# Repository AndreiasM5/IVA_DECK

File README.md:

<div align="center">

# IVA DECK

### A custom ESP32 macro keyboard with a desktop companion and behavioral recognition

**9 mechanical keys · 3 volume controls · LCD + microSD · USB / Bluetooth · Python + PyQt6**

[Download Windows app](https://github.com/AndreiasM5/IVA_DECK/releases/latest) · [Install V5](docs/windows-app-v5.ro.md) · [Demo](docs/media/iva-deck-demo.mp4) · [Get started](docs/getting-started.md) · [Hardware](docs/hardware.md) · [Protocol](docs/protocol.md) · [AI experiment](docs/behavioral-recognition.md) · [Română](docs/README.ro.md)

**Designed and built by Ioan-Andrei Ivașcu**

</div>

IVA DECK combines a custom PCB, ESP32 electronics, embedded software, a Windows desktop application, and a behavioral recognition experiment. Nine programmable keys handle shortcuts and media actions, three physical knobs control application volume, and the companion app exposes the display, storage, buzzer, and proximity sensor.

The original academic project was presented in June 2025 at the Faculty of Mathematics and Computer Science, University of Bucharest, as **“Tastatură Inteligentă cu Recunoaștere Comportamentală asistată de AI.”**

## Windows app — V5

**[Download the Windows installer](https://github.com/AndreiasM5/IVA_DECK/releases/latest)** · [Ghid de instalare în română](docs/windows-app-v5.ro.md) · [Source and build instructions](SOFTWARE/APP/v5/)

Install **IVA-DECK-5.0.0-Setup-x64.exe**, pair your deck over Bluetooth or connect USB, then select its port in **Conexiune**. No separate Python installation is needed. Supports Windows 10 21H2+ / Windows 11 x64.

V5 adds a purple/pink interface, macro labels and assignment dialogs, an editable macro library and three animated potentiometers. The **Volum** page selects audio targets. Macros, audio targets and the last port are saved per user. AI and SD-image workflows are outside this release. V4 and the historical project documentation remain available.

The V5 application is free software under [GPLv3](SOFTWARE/APP/v5/LICENSE). This first installer is unsigned; see the release notes and SHA-256 checksums.

## See it working

**[Full demonstration with audio — 2 min 8 sec](docs/media/iva-deck-demo.mp4)**

The recording shows key presses, macro configuration, audio controls, proximity feedback, display interaction, and behavioral analysis. The GIF is a silent excerpt. Open or download the MP4 for the complete recording.

## What I built

| Layer | Contribution |
| --- | --- |
| Hardware | Custom KiCad PCBs, 3×3 key matrix, three potentiometers, peripheral integration, and enclosure |
| Embedded | ESP32 peripheral control and bidirectional serial messaging |
| Desktop | PyQt6 interface for macros, Windows volume control, device commands, and logging |
| AI experiment | Feature extraction and Random Forest recognition using keys, timing, distance, and volume |

## Desktop companion

| Live keys | Application volume |
| --- | --- |
|  |  |

| Macros | Display and storage |
| --- | --- |
|  |  |

The application targets **Windows**, using `pycaw` and Windows COM APIs for audio-session control. Its interface is in Romanian.

<details>
<summary>More application screens: proximity and connections</summary>

| Proximity | Connection settings |
| --- | --- |
|  |  |

</details>

## Architecture

```mermaid
flowchart LR
  Keys[3x3 matrix] -->|GPIO| ESP[ESP32]
  Knobs[Three knobs] -->|ADC| ESP
  ToF[VL53L0X] -->|I2C| ESP
  ESP -->|SPI| LCD[ST7789]
  ESP <-->|SPI| SD[microSD]
  ESP --> Buzzer[Buzzer]
  ESP <-->|JSON over USB or Bluetooth serial| App[PyQt6 app]
  App --> Macros[OS macros]
  App --> Audio[Windows audio]
  App --> Logs[Local logs]
  Logs --> Features[Feature extraction]
  Features --> RF[Random Forest]
```

The INMP441 microphone is included in the hardware design. Full host audio streaming and voice control are unfinished, rather than demonstrated features.

## From prototype to PCB

| PCB layout | Enclosure design |
| --- | --- |
|  |  |

Original hardware iterations are preserved. Start with [revision v6](HARDWARE/v6_esp32/) and the [hardware guide](docs/hardware.md).

## Explore

| Material | Contents |
| --- | --- |
| [Getting started](docs/getting-started.md) | Windows installation and connections |
| [Desktop source](SOFTWARE/APP/v4/iva_key_app/) | PyQt6 app and configuration |
| [ESP32 v6](SOFTWARE/DECK/v6_esp32/) | Sketches and firmware status |
| [KiCad hardware](HARDWARE/) | Schematics, layouts, and production exports |
| [Protocol](docs/protocol.md) | Host messages and commands |
| [Behavioral recognition](docs/behavioral-recognition.md) | Training workflow and evaluation limits |
| [Thesis](Documentation.pdf) | Original 52-page Romanian academic documentation |
| [Presentation PDF](docs/presentation-ro.pdf) | Romanian defense presentation |
| [Editable slides](Presentation.pptx) | Original slide deck |

## Project status

The desktop source, AI script, KiCad projects, and peripheral tests are available. A complete **historical ESP32 sketch was recovered from the author's development chat** and is included with provenance and compatibility notes. It has not been verified as the exact firmware used in the demo; see the [firmware status](SOFTWARE/DECK/v6_esp32/README.md).

The thesis reports approximately **70% behavioral recognition** in its experiment. This is a historical reported result, not a newly reproduced benchmark or an authentication guarantee. See the [AI guide](docs/behavioral-recognition.md).

Documentation and media were checked against the supplied materials and repository source. Fresh hardware operation, firmware compilation, and desktop integration have not been revalidated during this documentation update.

## Author

**Ioan-Andrei Ivașcu** · [@AndreiasM5](https://github.com/AndreiasM5)

Custom hardware, firmware development, companion software, and behavioral-recognition research for the original academic project.

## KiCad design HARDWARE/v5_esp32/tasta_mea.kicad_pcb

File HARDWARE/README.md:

# IVA DECK hardware

Start with [revision v6](v6_esp32/) and the [hardware guide](../docs/hardware.md).

Original directories preserve early Arduino Micro designs and later ESP32 iterations. Use editable KiCad sources for review; screenshots in `docs/media/` are explanatory references. Manufacturing exports have not been regenerated during this update.

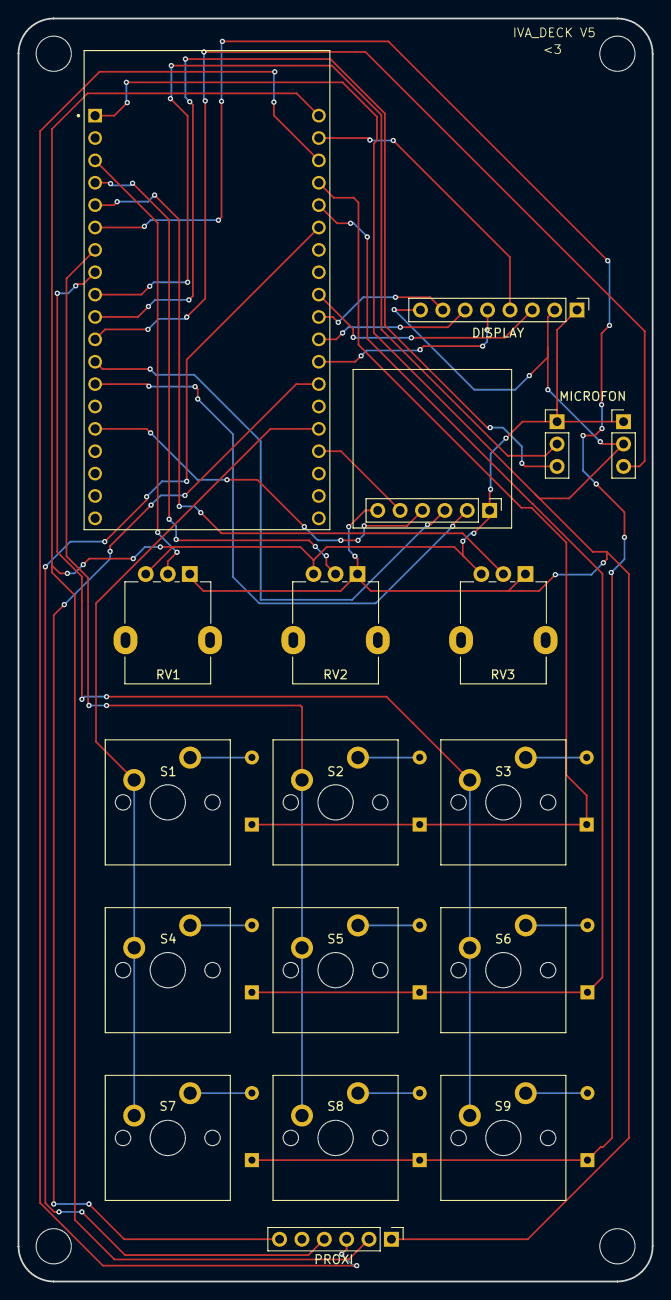
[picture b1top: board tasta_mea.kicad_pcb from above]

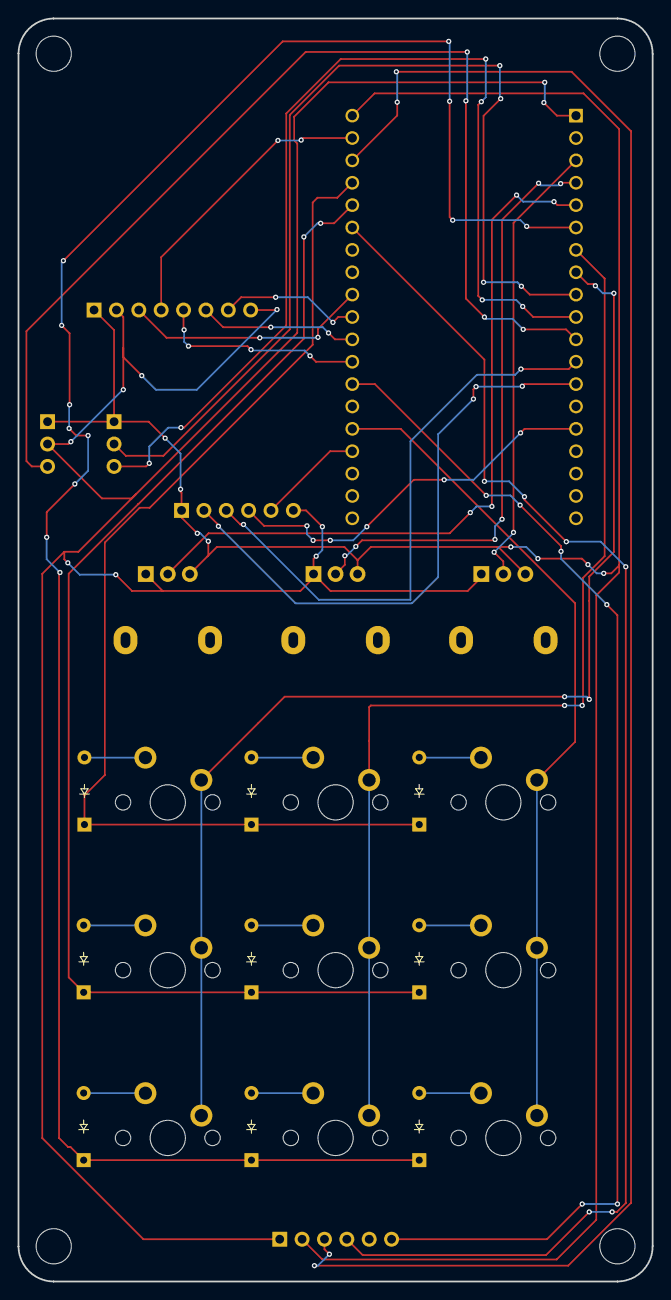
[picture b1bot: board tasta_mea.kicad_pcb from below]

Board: 2 copper layers, 72.0 x 143.4 mm, 27 parts (9 on the bottom side), 35 nets.

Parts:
D1, D2, D3, D4, D5, D6, D7, D8, D9: Diode; DO-35
DISPLAY: ST7789; PinHeader_1x08_P2.54mm_Vertical
J2: Card_reader; PinHeader_1x06_P2.54mm_Vertical
J4: IMNP441_Dreapta; PinHeader_1x03_P2.54mm_Vertical
MICROFON: IMNP441_stanga; PinHeader_1x03_P2.54mm_Vertical
PROXI: VL53L0X; PinHeader_1x06_P2.54mm_Vertical
RV1, RV2, RV3: R_Potentiometer; Potentiometer_Alpha_RD901F-40-00D_Single_Vertical
S1, S2, S3, S4, S5, S6, S7, S8, S9: Keyswitch; MX_PCB_1.00u
U3: ESP32-DEVKITC-32D; MODULE_ESP32-DEVKITC-32D

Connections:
C_clk: J2.3, U3.J2-12 (IO14)
C_cs: J2.5, U3.J3-16 (IO15)
C_gnd: DISPLAY.1, J2.1, J4.1, MICROFON.1, PROXI.2, RV1.3, RV2.3, RV3.3, U3.J3-1 (GND3)
C_miso: J2.2, U3.J2-13 (IO12)
C_mosi: J2.4, U3.J2-15 (IO13)
C_vcc: DISPLAY.2, DISPLAY.8, J2.6, J4.2, PROXI.1, RV1.1, RV2.1, RV3.1, U3.J2-1 (3V3)
D_CS: DISPLAY.7, U3.J3-10 (IO5)
D_DC: DISPLAY.6, U3.J3-11 (IO17)
D_RST: DISPLAY.5, U3.J3-12 (IO16)
D_SCL: DISPLAY.3, U3.J3-9 (IO18)
D_SDA: DISPLAY.4, U3.J3-2 (IO23)
M_SCK: MICROFON.3, U3.J2-10 (IO26)
M_SD: J4.3, U3.J2-11 (IO27)
M_WS: MICROFON.2, U3.J2-9 (IO25)
unnamed: D1.2 (A), S1.2
unnamed: D2.2 (A), S2.2
unnamed: D3.2 (A), S3.2
unnamed: D4.2 (A), S4.2
unnamed: D5.2 (A), S5.2
unnamed: D6.2 (A), S6.2
unnamed: D7.2 (A), S7.2
unnamed: D8.2 (A), S8.2
unnamed: D9.2 (A), S9.2
P_SCL: PROXI.3, U3.J3-3 (IO22)
P_SDA: PROXI.4, U3.J3-6 (IO21)
P_XSHUT: PROXI.6, U3.J3-13 (IO4)
col 1: S1.1, S4.1, S7.1, U3.J3-15 (IO2)
col 2: S2.1, S5.1, S8.1, U3.J2-7 (IO32)
col 3: S3.1, S6.1, S9.1, U3.J2-8 (IO33)
row 1: D1.1 (K), D2.1 (K), D3.1 (K), U3.J3-4 (TXD0)
row 2: D4.1 (K), D5.1 (K), D6.1 (K), U3.J3-5 (RXD0)
row 3: D7.1 (K), D8.1 (K), D9.1 (K), U3.J2-6 (IO35)
vol 1: RV1.2, U3.J2-3 (SENSOR_VP)
vol 2: RV2.2, U3.J2-4 (SENSOR_VN)
vol 3: RV3.2, U3.J2-5 (IO34)

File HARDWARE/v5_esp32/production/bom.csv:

Designator,Footprint,Quantity,Value,LCSC Part #
"D1, D2, D3, D4, D5, D6, D7, D8, D9",DO-35,9,Diode,
DISPLAY,PinHeader_1x08_P2.54mm_Vertical,1,ST7789,
J2,PinHeader_1x06_P2.54mm_Vertical,1,Card_reader,
J4,PinHeader_1x03_P2.54mm_Vertical,1,IMNP441_Dreapta,
MICROFON,PinHeader_1x03_P2.54mm_Vertical,1,IMNP441_stanga,
PROXI,PinHeader_1x06_P2.54mm_Vertical,1,VL53L0X,
"RV1, RV2, RV3",Potentiometer_Alpha_RD901F-40-00D_Single_Vertical,3,R_Potentiometer,
"S1, S2, S3, S4, S5, S6, S7, S8, S9",MX_PCB_1.00u,9,Keyswitch,
U3,MODULE_ESP32-DEVKITC-32D,1,ESP32-DEVKITC-32D,

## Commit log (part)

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2025-03-27 hardware deck v1_arduino_micro
2025-03-27 hardware deck v1.2_arduino_micro
2025-03-27 hardware deck v2_esp32
2025-03-27 matix and volume test for esp32
2025-03-27 lcd test for esp32
2025-04-09 hardware deck v4_esp32
2025-04-24 hardware deck v5_esp32
2025-06-12 hardware deck v6_esp32
2025-06-12 tests for V6
2025-06-12 firmware tests for V6
2025-08-14 v4 of app
2025-08-14 presentation and documentation
